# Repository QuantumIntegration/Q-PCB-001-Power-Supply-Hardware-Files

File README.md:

# Quantum DIY Kit Hardware Files - Power Supply
## Introduction

This repository contains all the hardware files necessary to build the PCBs and assemble the DIY kits. The PCBs can be ordered from for example [JLCPCB](https://jlcpcb.com/) or [PCBWay](https://www.pcbway.com/). The components can be sourced mostly from [Amazon](https://amazon.com/) or [Digikey](https://digikey.com/), according to the links in the BOM file.

## Download the correct revision

If you are nor familiar with the git version control system, please follow these simple steps to download your version of the DIY kit

<em>1. Click the branch button</em>

<em>2. Select the branch matching your revision</em>

<em>3. Click the Code button</em>

<em>4. Download the ZIP and extract it on your machine</em>

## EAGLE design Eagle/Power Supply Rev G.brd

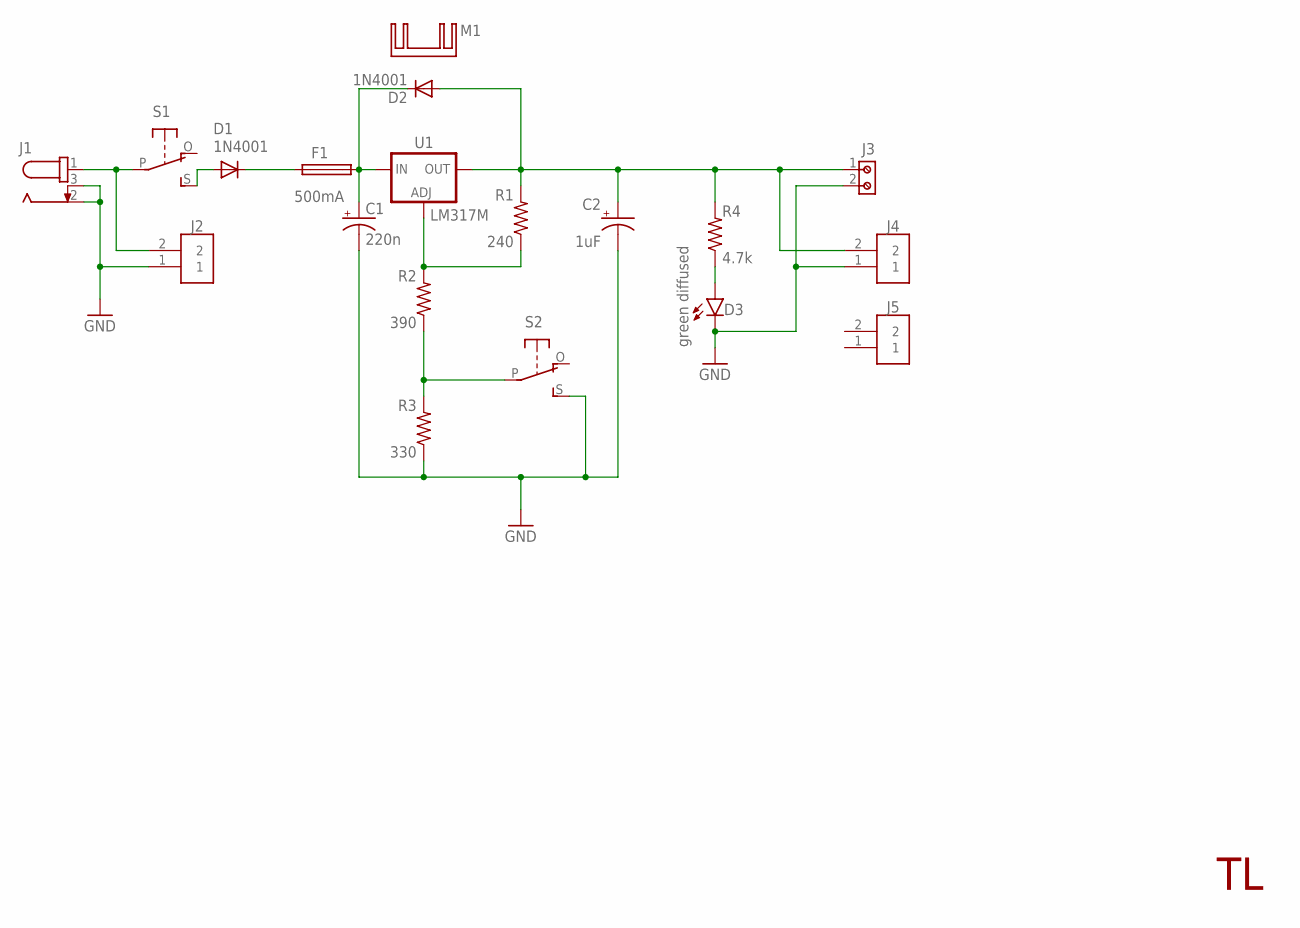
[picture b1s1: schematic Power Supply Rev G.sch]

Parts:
C1: 220n; E2-4
C2: 1uF; E2-4
D1, D2: 1N4001; DO41-10
D3: green diffused; LED5MM
F1: 500mA; PTC-FUSE
J1: 694106301002
J2, J4, J5: 61300211121
J3: 691214110002
M1: TO220-HEATSINK; D03S
R1: 240; 0207/10
R2: 390; 0207/10
R3: 330; 0207/10
R4: 4.7k; 0207/10
S1, S2: SLIDE-SWITCHSIDE; EG1270-90
U1: LM317; 317TS; PARTNUMBER LM317M

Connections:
GND: C1.-, C2.-, D3.K (C), J1.2, J1.3, J2.1, J3.2, J4.1, R3.1, S2.S
unnamed: D1.A, S1.S
unnamed: J1.1, J2.2, S1.P
unnamed: D1.C, F1.1
unnamed: C1.+, D2.C, F1.2, U1.3 (IN)
unnamed: R1.1, R2.2, U1.1 (ADJ)
unnamed: C2.+, D2.A, J3.1, J4.2, R1.2, R4.2, U1.2 (OUT)
unnamed: R2.1, R3.2, S2.P
unnamed: D3.A, R4.1

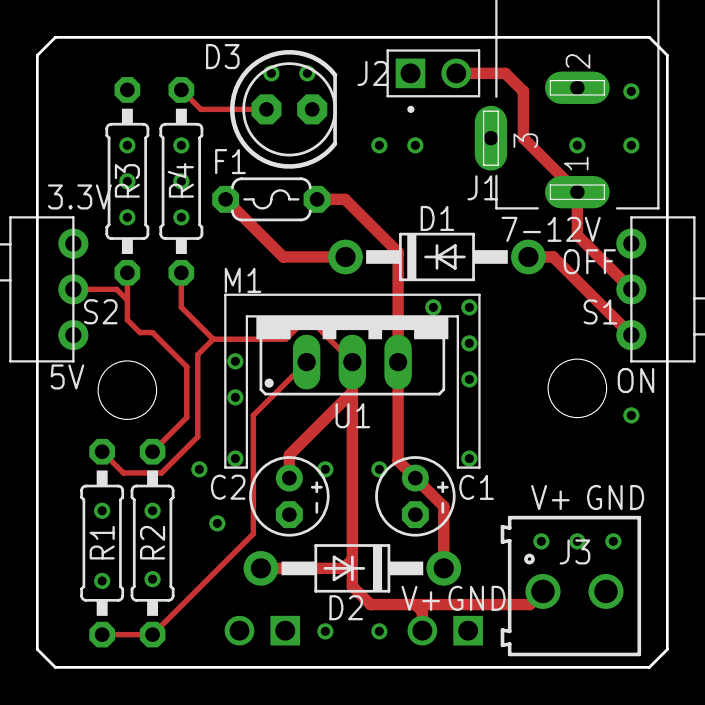
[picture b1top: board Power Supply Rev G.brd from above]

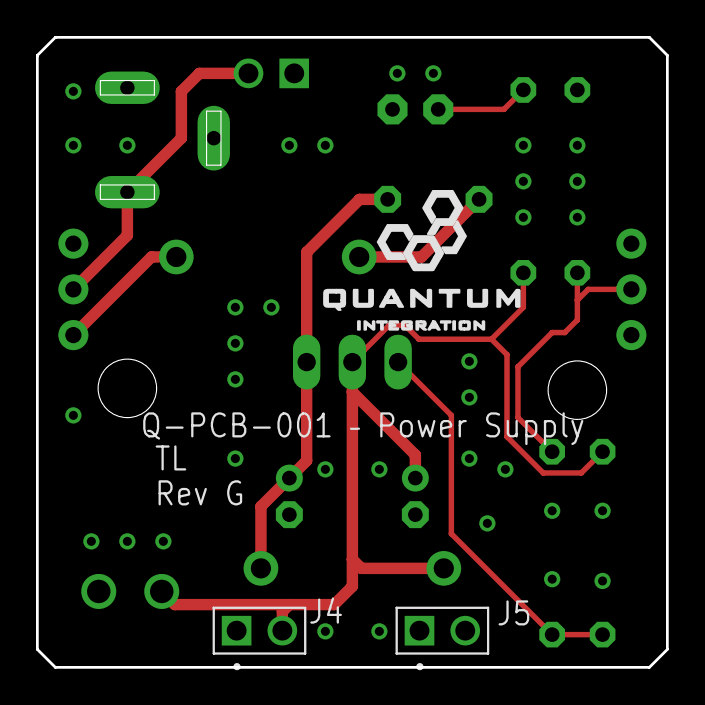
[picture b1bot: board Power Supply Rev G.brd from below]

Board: 2 copper layers, 35.0 x 35.0 mm, 19 parts (2 on the bottom side), 9 nets.

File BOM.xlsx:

Index | Part | Value | Quantity | Designators | Package | Comments | Specific Part Reference | Part Link Example
1 | Terminal |  | 1 | J3 |  | 3.50mm, 1x2 |  | https://www.digikey.com/product-detail/en/w%C3%BCrth-elektro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
2 | Barrell Jack |  | 1 | J1 |  | 2.1mm jack |  | https://www.digikey.com/products/en?keywords=694106301002
3 | Slide Switch |  | 2 | S1, S2 |  | 90 degree | EG1270 | https://www.digikey.com/product-detail/en/e-switch/EG1270/EG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
4 | Electrolytic Capacitor | 220n | 1 | C1 | E2-4 | H: 8mm, 50V |  | https://www.digikey.com/product-detail/en/nichicon/USP1H0R1M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
5 | Electrolytic Capacitor | 1u | 1 | C2 | E2-4 | H: 8mm, 50V |  | https://www.digikey.com/product-detail/en/nichicon/USA1H010M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
6 | Diode | 1-N4001 | 2 | D1, D2 |  |  |  | https://www.digikey.com/product-detail/en/comchip-technology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
7 | Resistor | 240 | 1 | R1 | 0207/10 | 1/4 W |  | https://www.amazon.com/SIQUK-Resistors-Resistor-Assortment-E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
8 | Resistor | 330 | 1 | R3 | 0207/10 | 1/4 W |  | https://www.amazon.com/SIQUK-Resistors-Resistor-Assortment-E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
9 | Resistor | 390 | 1 | R2 | 0207/10 | 1/4 W |  | https://www.amazon.com/SIQUK-Resistors-Resistor-Assortment-E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
10 | Resistor | 4.7k | 1 | R4 | 0207/10 | 1/4 W |  | https://www.amazon.com/SIQUK-Resistors-Resistor-Assortment-E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
11 | PTC Fuse | 500m | 1 | F1 |  | self reset |  | https://www.amazon.com/gp/product/B00X774PAY/ref=ppx_yo_dt_b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
12 | LED | green-diffused | 1 | D3 | 5mm |  |  | https://www.amazon.com/Diffused-Lighting-Electronics-Compone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
13 | LM317 |  | 1 | U1 | TO-220-3 |  | LM317T | https://www.digikey.com/product-detail/en/stmicroelectronics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
14 | Header |  | 3 | J2, J4, J5 | 0.1 | 1x2, male |  | https://www.amazon.com/MCIGICM-Header-2-45mm-Arduino-Connect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
15 | M3 Screw |  | 3 |  |  | 6mm |  | https://www.amazon.com/gp/product/B07CNF3W7B/ref=ppx_yo_dt_b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
16 | Heatsink |  | 1 | M1 |  |  |  | https://www.digikey.com/product-detail/en/aavid-thermal-divi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
17 | Thermal Pad |  | 1 |  |  | fits LM317 |  | https://www.digikey.com/product-detail/en/bergquist/HF115AC-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
18 | M3 Nut |  | 1 |  |  |  |  | https://www.amazon.com/gp/product/B07CNF3W7B/ref=ppx_yo_dt_b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
19 | Battery Harness |  | 1 |  |  | 2.1 mm plug |  | https://www.amazon.com/AKOAK-Battery-Button-Connector-Holder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

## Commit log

2021-03-15 optimized gitignore and added Readme
2021-03-15 initial commit to rev g
2021-03-16 readme and license edit
2021-03-16 added Eagle files
2021-03-16 edited readme title
2021-03-16 added preview to readme
2021-03-16 changed preview ratio
2021-04-26 changes to BOM for manufacturing
2021-08-17 added schematic as PDF

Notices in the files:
parts and their libraries:
Wurth_Connectors_WR-TBL Rising Cage Clam: Copyright: Würth Elektronik
